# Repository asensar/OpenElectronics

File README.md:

OpenElectronics
===============

Open Source Electronics Desings and Collections by aSensar

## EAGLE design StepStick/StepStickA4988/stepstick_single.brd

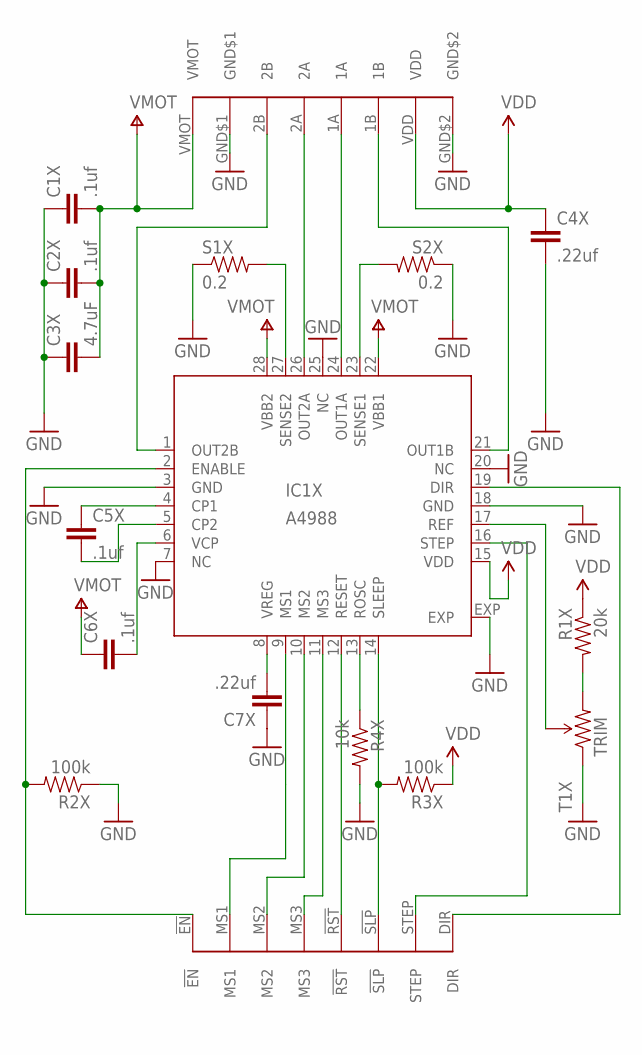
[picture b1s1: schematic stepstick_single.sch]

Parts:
C1X, C2X, C5X, C6X: .1uf; 0402-CAP
C3X: 4.7uF; 1206
C4X, C7X: .22uf; 0402-CAP
IC1X: A4988; QFN28ET
J1X: CLONOLU
R1X: 20k; 0402-RES
R2X, R3X: 100k; 0402-RES
R4X: 10k; 0402-RES
S1X, S2X: 0.2; 0805
T1X: TRIM; TRIMPOT-3MM

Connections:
GND: C1X.1, C2X.1, C3X.1, C4X.2, C7X.1, IC1X.3 (GND), IC1X.7 (NC), IC1X.18 (GND), IC1X.20 (NC), IC1X.25 (NC), IC1X.EXP, J1X.GND$1, J1X.GND$2, R2X.1, R4X.2, S1X.1, S2X.1, T1X.1 (CCW)
VDD: C4X.1, IC1X.15 (VDD), J1X.VDD, R1X.1, R3X.1
VMOT: C1X.2, C2X.2, C3X.2, C6X.1, IC1X.22 (VBB1), IC1X.28 (VBB2), J1X.VMOT
XCP1: C5X.1, IC1X.4 (CP1)
XCP2: C5X.2, IC1X.5 (CP2)
XDIR: IC1X.19 (DIR), J1X.DIR
XENABLE: IC1X.2 (ENABLE), J1X.!EN, R2X.2
XMS1: IC1X.9 (MS1), J1X.MS1
XMS2: IC1X.10 (MS2), J1X.MS2
XMS3: IC1X.11 (MS3), J1X.MS3
XOUT1A: IC1X.24 (OUT1A), J1X.1A
XOUT1B: IC1X.21 (OUT1B), J1X.1B
XOUT2A: IC1X.26 (OUT2A), J1X.2A
XOUT2B: IC1X.1 (OUT2B), J1X.2B
XREF: IC1X.17 (REF), T1X.2 (WIPER)
XREF2: R1X.2, T1X.3 (CW)
XRESET: IC1X.12 (RESET), J1X.!RST
XROSC: IC1X.13 (ROSC), R4X.1
XSENSE1: IC1X.23 (SENSE1), S2X.2
XSENSE2: IC1X.27 (SENSE2), S1X.2
XSLEEP: IC1X.14 (SLEEP), J1X.!SLP, R3X.2
XSTEP: IC1X.16 (STEP), J1X.STEP
XVCP: C6X.2, IC1X.6 (VCP)
XVREG: C7X.2, IC1X.8 (VREG)

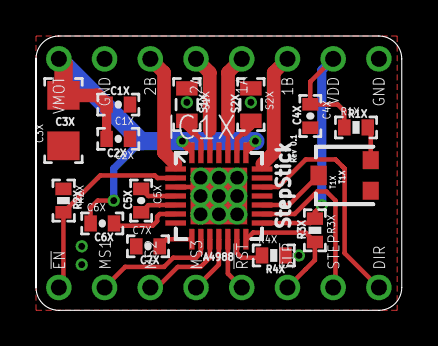
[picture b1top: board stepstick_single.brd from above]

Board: 2 copper layers, 20.3 x 15.2 mm, 16 parts (0 on the bottom side), 24 nets.

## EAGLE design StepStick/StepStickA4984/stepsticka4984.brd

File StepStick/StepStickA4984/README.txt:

http://www.thingiverse.com/thing:33766

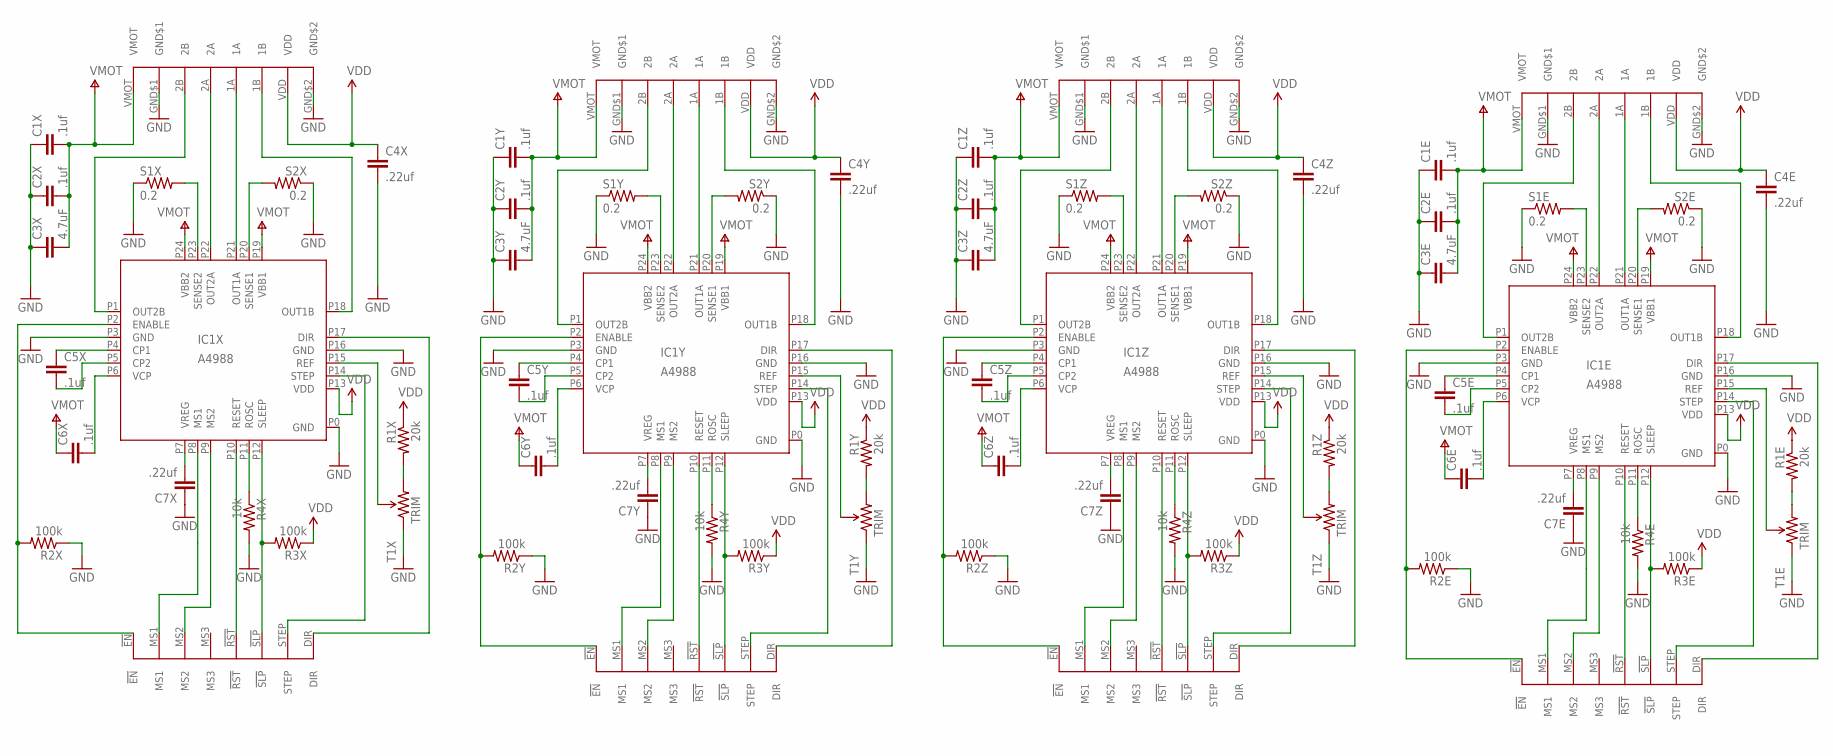
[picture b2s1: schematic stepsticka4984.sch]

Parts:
C1E, C1X, C1Y, C1Z, C2E, C2X, C2Y, C2Z, C5E, C5X, C5Y, C5Z, C6E, C6X, C6Y, C6Z: .1uf; 0402-CAP
C3E, C3X, C3Y, C3Z: 4.7uF; 1206
C4E, C4X, C4Y, C4Z, C7E, C7X, C7Y, C7Z: .22uf; 0402-CAP
IC1E, IC1X, IC1Y, IC1Z: A4988; QFN24ES
J1E, J1X, J1Y, J1Z: CLONOLU
R1E, R1X, R1Y, R1Z: 20k; 0402-RES
R2E, R2X, R2Y, R2Z, R3E, R3X, R3Y, R3Z: 100k; 0402-RES
R4E, R4X, R4Y, R4Z: 10k; 0402-RES
S1E, S1X, S1Y, S1Z, S2E, S2X, S2Y, S2Z: 0.2; 0805
T1E, T1X, T1Y, T1Z: TRIM; TRIMPOT-3MM

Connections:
ECP1: C5E.1, IC1E.P4 (CP1)
ECP2: C5E.2, IC1E.P5 (CP2)
EDIR: IC1E.P17 (DIR), J1E.DIR
EENABLE: IC1E.P2 (ENABLE), J1E.!EN, R2E.2
EMS1: IC1E.P8 (MS1), J1E.MS1
EMS2: IC1E.P9 (MS2), J1E.MS2
EOUT1A: IC1E.P21 (OUT1A), J1E.1A
EOUT1B: IC1E.P18 (OUT1B), J1E.1B
EOUT2A: IC1E.P22 (OUT2A), J1E.2A
EOUT2B: IC1E.P1 (OUT2B), J1E.2B
EREF: IC1E.P15 (REF), T1E.2 (WIPER)
EREF2: R1E.2, T1E.3 (CW)
ERESET: IC1E.P10 (RESET), J1E.!RST
EROSC: IC1E.P11 (ROSC), R4E.1
ESENSE1: IC1E.P20 (SENSE1), S2E.2
ESENSE2: IC1E.P23 (SENSE2), S1E.2
ESLEEP: IC1E.P12 (SLEEP), J1E.!SLP, R3E.2
ESTEP: IC1E.P14 (STEP), J1E.STEP
EVCP: C6E.2, IC1E.P6 (VCP)
EVREG: C7E.2, IC1E.P7 (VREG)
GND: C1E.1, C1X.1, C1Y.1, C1Z.1, C2E.1, C2X.1, C2Y.1, C2Z.1, C3E.1, C3X.1, C3Y.1, C3Z.1, C4E.2, C4X.2, C4Y.2, C4Z.2, C7E.1, C7X.1, C7Y.1, C7Z.1, IC1E.P0 (GND), IC1E.P3 (GND), IC1E.P16 (GND), IC1X.P0 (GND), IC1X.P3 (GND), IC1X.P16 (GND), IC1Y.P0 (GND), IC1Y.P3 (GND), IC1Y.P16 (GND), IC1Z.P0 (GND), IC1Z.P3 (GND), IC1Z.P16 (GND), J1E.GND$1, J1E.GND$2, J1X.GND$1, J1X.GND$2, J1Y.GND$1, J1Y.GND$2, J1Z.GND$1, J1Z.GND$2, R2E.1, R2X.1, R2Y.1, R2Z.1, R4E.2, R4X.2, R4Y.2, R4Z.2, S1E.1, S1X.1, S1Y.1, S1Z.1, S2E.1, S2X.1, S2Y.1, S2Z.1, T1E.1 (CCW), T1X.1 (CCW), T1Y.1 (CCW), T1Z.1 (CCW)
VDD: C4E.1, C4X.1, C4Y.1, C4Z.1, IC1E.P13 (VDD), IC1X.P13 (VDD), IC1Y.P13 (VDD), IC1Z.P13 (VDD), J1E.VDD, J1X.VDD, J1Y.VDD, J1Z.VDD, R1E.1, R1X.1, R1Y.1, R1Z.1, R3E.1, R3X.1, R3Y.1, R3Z.1
VMOT: C1E.2, C1X.2, C1Y.2, C1Z.2, C2E.2, C2X.2, C2Y.2, C2Z.2, C3E.2, C3X.2, C3Y.2, C3Z.2, C6E.1, C6X.1, C6Y.1, C6Z.1, IC1E.P19 (VBB1), IC1E.P24 (VBB2), IC1X.P19 (VBB1), IC1X.P24 (VBB2), IC1Y.P19 (VBB1), IC1Y.P24 (VBB2), IC1Z.P19 (VBB1), IC1Z.P24 (VBB2), J1E.VMOT, J1X.VMOT, J1Y.VMOT, J1Z.VMOT
XCP1: C5X.1, IC1X.P4 (CP1)
XCP2: C5X.2, IC1X.P5 (CP2)
XDIR: IC1X.P17 (DIR), J1X.DIR
XENABLE: IC1X.P2 (ENABLE), J1X.!EN, R2X.2
XMS1: IC1X.P8 (MS1), J1X.MS1
XMS2: IC1X.P9 (MS2), J1X.MS2
XOUT1A: IC1X.P21 (OUT1A), J1X.1A
XOUT1B: IC1X.P18 (OUT1B), J1X.1B
XOUT2A: IC1X.P22 (OUT2A), J1X.2A
XOUT2B: IC1X.P1 (OUT2B), J1X.2B
XOUT2B1: IC1Y.P1 (OUT2B), J1Y.2B
XREF: IC1X.P15 (REF), T1X.2 (WIPER)
XREF2: R1X.2, T1X.3 (CW)
XRESET: IC1X.P10 (RESET), J1X.!RST
XROSC: IC1X.P11 (ROSC), R4X.1
XSENSE1: IC1X.P20 (SENSE1), S2X.2
XSENSE2: IC1X.P23 (SENSE2), S1X.2
XSLEEP: IC1X.P12 (SLEEP), J1X.!SLP, R3X.2
XSTEP: IC1X.P14 (STEP), J1X.STEP
XVCP: C6X.2, IC1X.P6 (VCP)
XVREG: C7X.2, IC1X.P7 (VREG)
YCP1: C5Y.1, IC1Y.P4 (CP1)
YCP2: C5Y.2, IC1Y.P5 (CP2)
YDIR1: IC1Y.P17 (DIR), J1Y.DIR
YENABLE: IC1Y.P2 (ENABLE), J1Y.!EN, R2Y.2
YMS1: IC1Y.P8 (MS1), J1Y.MS1
YMS2: IC1Y.P9 (MS2), J1Y.MS2
YOUT1A: IC1Y.P21 (OUT1A), J1Y.1A
YOUT1B: IC1Y.P18 (OUT1B), J1Y.1B
YOUT2A: IC1Y.P22 (OUT2A), J1Y.2A
YREF: IC1Y.P15 (REF), T1Y.2 (WIPER)
YREF1: R1Y.2, T1Y.3 (CW)
YRESET: IC1Y.P10 (RESET), J1Y.!RST
YROSC: IC1Y.P11 (ROSC), R4Y.1
YSENSE1: IC1Y.P20 (SENSE1), S2Y.2
YSENSE2: IC1Y.P23 (SENSE2), S1Y.2
YSLEEP: IC1Y.P12 (SLEEP), J1Y.!SLP, R3Y.2
YSTEP: IC1Y.P14 (STEP), J1Y.STEP
YVCP: C6Y.2, IC1Y.P6 (VCP)
YVREG: C7Y.2, IC1Y.P7 (VREG)
ZCP1: C5Z.1, IC1Z.P4 (CP1)
ZCP2: C5Z.2, IC1Z.P5 (CP2)
ZDIR: IC1Z.P17 (DIR), J1Z.DIR
ZENABLE: IC1Z.P2 (ENABLE), J1Z.!EN, R2Z.2
ZMS1: IC1Z.P8 (MS1), J1Z.MS1
ZMS2: IC1Z.P9 (MS2), J1Z.MS2
ZOUT1A: IC1Z.P21 (OUT1A), J1Z.1A
ZOUT1B: IC1Z.P18 (OUT1B), J1Z.1B
ZOUT2A: IC1Z.P22 (OUT2A), J1Z.2A
ZOUT2B: IC1Z.P1 (OUT2B), J1Z.2B
ZREF: IC1Z.P15 (REF), T1Z.2 (WIPER)
ZREF2: R1Z.2, T1Z.3 (CW)
ZRESET: IC1Z.P10 (RESET), J1Z.!RST
ZROSC: IC1Z.P11 (ROSC), R4Z.1
ZSENSE1: IC1Z.P20 (SENSE1), S2Z.2
ZSENSE2: IC1Z.P23 (SENSE2), S1Z.2
ZSLEEP: IC1Z.P12 (SLEEP), J1Z.!SLP, R3Z.2
ZSTEP: IC1Z.P14 (STEP), J1Z.STEP
ZVCP: C6Z.2, IC1Z.P6 (VCP)
ZVREG: C7Z.2, IC1Z.P7 (VREG)

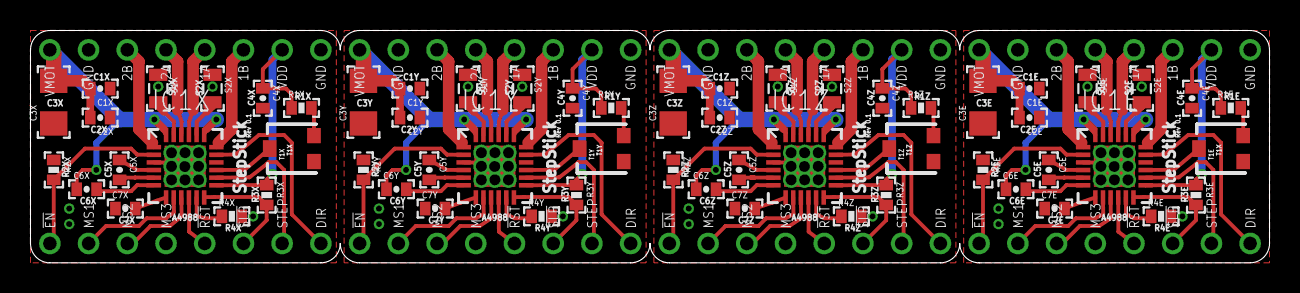
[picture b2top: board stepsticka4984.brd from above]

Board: 2 copper layers, 81.3 x 15.2 mm, 64 parts (0 on the bottom side), 83 nets.

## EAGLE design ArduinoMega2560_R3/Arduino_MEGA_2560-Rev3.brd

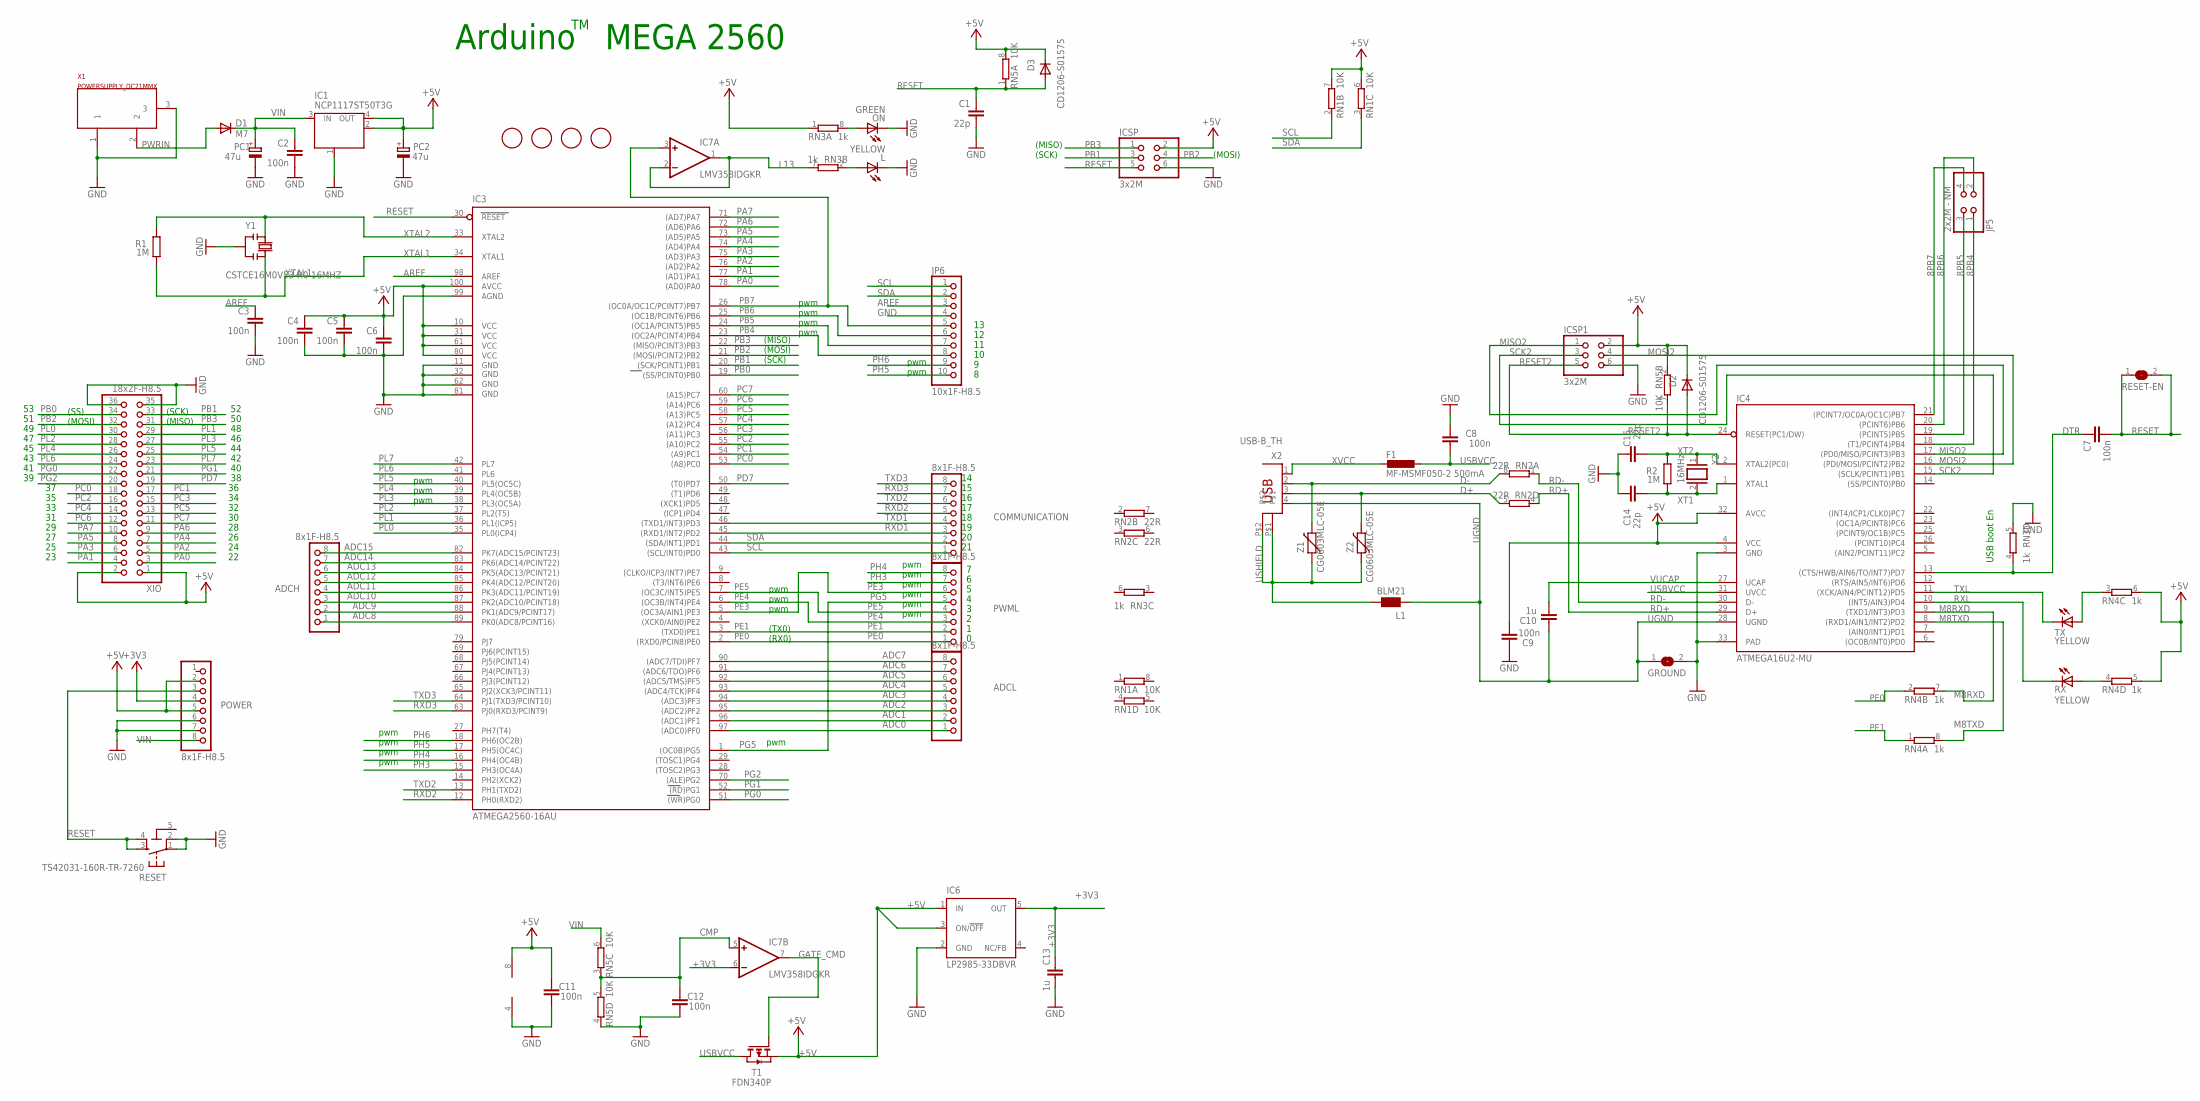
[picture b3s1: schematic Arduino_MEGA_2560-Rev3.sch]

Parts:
ADCH: 8x1F-H8.5; 1X08
ADCL: 8x1F-H8.5; 1X08
C1, C14, C15: 22p; C0603-ROUND
C2, C3, C4, C5, C6, C7, C8, C9, C11, C12: 100n; C0603-ROUND
C10, C13: 1u; C0603-ROUND
COMMUNICATION: 8x1F-H8.5; 1X08
D1: M7; SMB
D2, D3: CD1206-S01575; MINIMELF
F1: MF-MSMF050-2 500mA; L1812
FD1, FD2, FD3, FD4: FIDUCIALMOUNT; FIDUCIA-MOUNT
GROUND: SJ
IC1: NCP1117ST50T3G; SOT223
IC3: ATMEGA2560-16AU; TQFP100
IC4: ATMEGA16U2-MU; MLF32
IC6: LP2985-33DBVR; SOT23-DBV
IC7: LMV358IDGKR; MSOP08
ICSP, ICSP1: 3x2M; 2X03
JP5: 2x2M - NM; 2X02
JP6: 10x1F-H8.5; 1X10
L: YELLOW; CHIP-LED0805
L1: BLM21; 0805
ON: GREEN; CHIP-LED0805
PC1, PC2: 47u; PANASONIC_D
POWER: 8x1F-H8.5; 1X08
PWML: 8x1F-H8.5; 1X08
R1, R2: 1M; R0603-ROUND
RESET: TS42031-160R-TR-7260; TS42
RESET-EN: SJ
RN1, RN5: 10K; CAT16
RN2: 22R; CAY16
RN3, RN4: 1k; CAY16
RX: YELLOW; CHIP-LED0805
T1: FDN340P; SOT-23
TX: YELLOW; CHIP-LED0805
X1: POWERSUPPLY_DC21MMX; POWERSUPPLY_DC-21MM
X2: USB-B_TH; PN61729
XIO: 18x2F-H8.5; 2X18
Y1: CSTCE16M0V53-R0 16MHZ; RESONATOR
Y2: 16MHz; QS
Z1, Z2: CG0603MLC-05E; CT/CN0603

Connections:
5-GND: RESET.5 (5-GND)
8PB4: IC4.18 ((T1/PCINT4)PB4), JP5.1
8PB5: IC4.19 ((PCINT5)PB5), JP5.3
8PB6: IC4.20 ((PCINT6)PB6), JP5.2
8PB7: IC4.21 ((PCINT7/OC0A/OC1C)PB7), JP5.4
+3V3: C13.2, IC6.5 (OUT), IC7.6 (-IN), POWER.4
+5V: C4.1, C5.1, C6.1, C9.1, C11.2, D2.C, D3.C, IC1.2 (OUT), IC1.4 (OUT), IC3.10 (VCC), IC3.31 (VCC1), IC3.61 (VCC2), IC3.80 (VCC3), IC3.100 (AVCC), IC4.4 (VCC), IC4.32 (AVCC), IC6.1 (IN), IC6.3 (ON/!OFF), IC7.8 (V+), ICSP.2, ICSP1.2, PC2.+, POWER.2, POWER.5, RN1.6 (2), RN1.7 (2), RN3.1, RN4.5 (2), RN4.6 (2), RN5.2 (1), RN5.8 (2), T1.2 (S), XIO.1, XIO.2
ADC0: ADCL.1, IC3.97 ((ADC0)PF0)
ADC1: ADCL.2, IC3.96 ((ADC1)PF1)
ADC2: ADCL.3, IC3.95 ((ADC2)PF2)
ADC3: ADCL.4, IC3.94 ((ADC3)PF3)
ADC4: ADCL.5, IC3.93 ((ADC4/TCK)PF4)
ADC5: ADCL.6, IC3.92 ((ADC5/TMS)PF5)
ADC6: ADCL.7, IC3.91 ((ADC6/TDO)PF6)
ADC7: ADCL.8, IC3.90 ((ADC7/TDI)PF7)
ADC8: ADCH.1, IC3.89 (PK0(ADC8/PCINT16))
ADC9: ADCH.2, IC3.88 (PK1(ADC9/PCINT17))
ADC10: ADCH.3, IC3.87 (PK2(ADC10/PCINT18))
ADC11: ADCH.4, IC3.86 (PK3(ADC11/PCINT19))
ADC12: ADCH.5, IC3.85 (PK4(ADC12/PCINT20))
ADC13: ADCH.6, IC3.84 (PK5(ADC13/PCINT21))
ADC14: ADCH.7, IC3.83 (PK6(ADC14/PCINT22))
ADC15: ADCH.8, IC3.82 (PK7(ADC15/PCINT23))
AREF: C3.1, IC3.98 (AREF), JP6.3
CMP: C12.2, IC7.5 (+IN), RN5.3 (1), RN5.5 (2)
D+: RN2.5 (2), X2.3, Z2.2
D-: RN2.8 (2), X2.2, Z1.2
DTR: C7.1, IC4.13 ((CTS/HWB/AIN6/TO/INT7)PD7), RN3.4 (1)
GATE_CMD: IC7.7 (OUT), T1.3 (G)
GND: C1.2, C2.2, C3.2, C4.2, C5.2, C6.2, C8.2, C9.2, C11.1, C12.1, C13.1, C14.2, C15.2, GROUND.2, IC1.1 (GND/ADJ), IC3.11 (GND), IC3.32 (GND1), IC3.62 (GND2), IC3.81 (GND3), IC3.99 (AGND), IC4.3 (GND), IC4.33 (PAD), IC6.2 (GND), IC7.4 (V-), ICSP.6, ICSP1.6, JP6.4, L.C, ON.C, PC1.-, PC2.-, POWER.6, POWER.7, RESET.1, RESET.2, RN3.5 (2), RN5.4 (1), X1.1, X1.3, XIO.35, XIO.36, Y1.2
L13: IC7.1 (OUT), IC7.2 (-IN), RN3.7 (2)
M8RXD: IC4.9 ((TXD1/INT3)PD3), RN4.7 (2)
M8TXD: IC4.8 ((RXD1/AIN1/INT2)PD2), RN4.8 (2)
MISO2: IC4.17 ((PD0/MISO/PCINT3)PB3), ICSP1.1
MOSI2: IC4.16 ((PDI/MOSI/PCINT2)PB2), ICSP1.4
unnamed: L.A, RN3.2 (1)
unnamed: ON.A, RN3.8 (2)
unnamed: RN4.4 (1), RX.A
unnamed: RN4.3 (1), TX.A
PA0: IC3.78 ((AD0)PA0), XIO.3
PA1: IC3.77 ((AD1)PA1), XIO.4
PA2: IC3.76 ((AD2)PA2), XIO.5
PA3: IC3.75 ((AD3)PA3), XIO.6
PA4: IC3.74 ((AD4)PA4), XIO.7
PA5: IC3.73 ((AD5)PA5), XIO.8
PA6: IC3.72 ((AD6)PA6), XIO.9
PA7: IC3.71 ((AD7)PA7), XIO.10
PB0: IC3.19 ((SS/PCINT0)PB0), XIO.34
PB1: IC3.20 ((SCK/PCINT1)PB1), ICSP.3, XIO.33
PB2: IC3.21 ((MOSI/PCINT2)PB2), ICSP.4, XIO.32
PB3: IC3.22 ((MISO/PCINT3)PB3), ICSP.1, XIO.31
PB4: IC3.23 ((OC2A/PCINT4)PB4), JP6.8
PB5: IC3.24 ((OC1A/PCINT5)PB5), JP6.7
PB6: IC3.25 ((OC1B/PCINT6)PB6), JP6.6
PB7: IC3.26 ((OC0A/OC1C/PCINT7)PB7), IC7.3 (+IN), JP6.5
PC0: IC3.53 ((A8)PC0), XIO.18
PC1: IC3.54 ((A9)PC1), XIO.17
PC2: IC3.55 ((A10)PC2), XIO.16
PC3: IC3.56 ((A11)PC3), XIO.15
PC4: IC3.57 ((A12)PC4), XIO.14
PC5: IC3.58 ((A13)PC5), XIO.13
PC6: IC3.59 ((A14)PC6), XIO.12
PC7: IC3.60 ((A15)PC7), XIO.11
PD7: IC3.50 ((T0)PD7), XIO.19
PE0: IC3.2 ((RXD0/PCIN8)PE0), PWML.1, RN4.2 (1)
PE1: IC3.3 ((TXD0)PE1), PWML.2, RN4.1
PE3: IC3.5 ((OC3A/AIN1)PE3), PWML.6
PE4: IC3.6 ((OC3B/INT4)PE4), PWML.3
PE5: IC3.7 ((OC3C/INT5)PE5), PWML.4
PG0: IC3.51 ((WR)PG0), XIO.22
PG1: IC3.52 ((RD)PG1), XIO.21
PG2: IC3.70 ((ALE)PG2), XIO.20
PG5: IC3.1 ((OC0B)PG5), PWML.5
PH3: IC3.15 (PH3(OC4A)), PWML.7
PH4: IC3.16 (PH4(OC4B)), PWML.8
PH5: IC3.17 (PH5(OC4C)), JP6.10
PH6: IC3.18 (PH6(OC2B)), JP6.9
PL0: IC3.35 (PL0(ICP4)), XIO.30
PL1: IC3.36 (PL1(ICP5)), XIO.29
PL2: IC3.37 (PL2(T5)), XIO.28
PL3: IC3.38 (PL3(OC5A)), XIO.27
PL4: IC3.39 (PL4(OC5B)), XIO.26
PL5: IC3.40 (PL5(OC5C)), XIO.25
PL6: IC3.41 (PL6), XIO.24
PL7: IC3.42 (PL7), XIO.23
PWRIN: D1.A, X1.2
RD+: IC4.29 (D+), RN2.4 (1)
RD-: IC4.30 (D-), RN2.1
RESET: C1.1, C7.2, D3.A, IC3.30 (RESET), ICSP.5, POWER.3, RESET.3, RESET.4, RESET-EN.1, RESET-EN.2, RN5.1
RESET2: D2.A, IC4.24 (RESET(PC1/DW)), ICSP1.5, RN5.7 (2)
RXD1: COMMUNICATION.3, IC3.45 ((RXD1/INT2)PD2)
RXD2: COMMUNICATION.5, IC3.12 (PH0(RXD2))
RXD3: COMMUNICATION.7, IC3.63 (PJ0(RXD3/PCINT9))
RXL: IC4.10 ((INT5/AIN3)PD4), RX.C
SCK2: IC4.15 ((SCLK/PCINT1)PB1), ICSP1.3
SCL: COMMUNICATION.1, IC3.43 ((SCL/INT0)PD0), JP6.1, RN1.2 (1)
SDA: COMMUNICATION.2, IC3.44 ((SDA/INT1)PD1), JP6.2, RN1.3 (1)
TXD1: COMMUNICATION.4, IC3.46 ((TXD1/INT3)PD3)
TXD2: COMMUNICATION.6, IC3.13 (PH1(TXD2))
TXD3: COMMUNICATION.8, IC3.64 (PJ1(TXD3/PCINT10))
TXL: IC4.11 ((XCK/AIN4/PCINT12)PD5), TX.C
UGND: C10.2, GROUND.1, IC4.28 (UGND), L1.1, X2.4
USBVCC: C8.1, F1.1, IC4.31 (UVCC), T1.1 (D)
USHIELD: L1.2, X2.P$1, X2.P$2, Z1.1, Z2.1
VIN: C2.1, D1.C, IC1.3 (IN), PC1.+, POWER.8, RN5.6 (2)
VUCAP: C10.1, IC4.27 (UCAP)
XT1: C14.1, IC4.1 (XTAL1), R2.1, Y2.2
XT2: C15.1, IC4.2 (XTAL2(PC0)), R2.2, Y2.1
XTAL1: IC3.34 (XTAL1), R1.1, Y1.3
XTAL2: IC3.33 (XTAL2), R1.2, Y1.1
XVCC: F1.2, X2.1

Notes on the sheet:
Arduino MEGA 2560
(SCK)
(MISO)
(MOSI)
pwm
(TX0)
(RX0)
(SS)
USB boot En

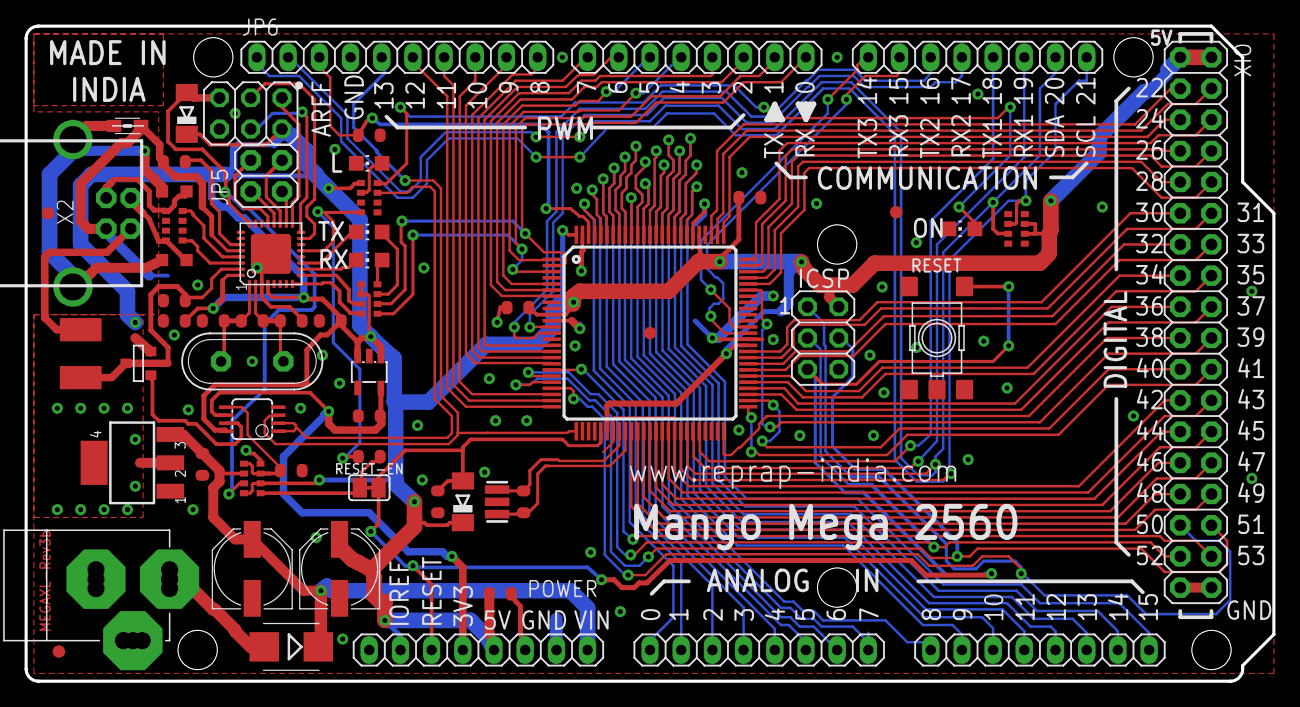
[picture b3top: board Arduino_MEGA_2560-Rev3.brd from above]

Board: 2 copper layers, 101.6 x 53.3 mm, 62 parts (1 on the bottom side), 110 nets.

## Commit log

2014-01-19 Added PCB desings of arduino mega r3, pcb heated bed Signed-off-by: aSensar <admin@asensar.com>
2014-01-19 Modified MK2a brd file and added asensar_greber_creator.cam, which combine functnality of both greb274x and excelon cam files Signed-off-by: aSensar <admin@asensar.com>
2014-01-19 Added the reprap-india.com url to bottom as well Signed-off-by: aSensar <admin@asensar.com>
2014-04-09 Added various stepsticks Signed-off-by: aSensar <admin@asensar.com>
